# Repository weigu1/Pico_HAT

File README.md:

# Pico-HAT: Connect your Raspi with the Pico through I²C

## All infos on: <http://www.weigu.lu/microcontroller/pico_hat/index.html>

## Some infos

The Pico connects to all the sensors and actuators and can act in `Real Time`. The Raspi can do the rest (Wifi, Webserver, MQTT, Display ...). The Pico is an I²C slave to the Raspi and the Raspi sends commands with a Python script to the Pico. An Arduino program on the Pico answers with sensor data or by switching an actuator.

As the Arduino IDE runs on a Raspi, both device (Raspi and Pico) can be reprogrammed via VNC from any computer, and I find this pretty amazing :).

### Features

+ The Raspi is connected through I²C with the Pico. Serial is prepared if needed (by adding 2 0&#8239;Ω resistors).

+ The Pico can be powered over USB (recommended if you want to reprogram it via Arduino IDE and VNC) or through the Raspi (5&#8239;V).

+ All GPIOs have the possibility to add a voltage divider to reduce the input voltage (e.g. 5&#8239;V to 3.3&#8239;V), or to add an external pull-down resistor.

+ All headers have beneath a ground pin, one or two power pins (3.3&#8239;V or 5&#8239;V; `H2` headers: 3.3&#8239;V and 5&#8239;V).

+ Additionally we get a RESET-button, an `SWD` header, 2 power header (3.3&#8239;V and 5&#8239;V), 2 Ground pins, an an 3V3_EN and ADC\_VREF pins.

### Circuit

The circuit is designed with KiCAD and is open hardware. The following headers are available:

| Name | Pin 1 | Pin 2 | Pin 3 | Pin 5 | Pin 5 | Pin 6 | Pin 7 |
|--|--|--|--|--|--|--|--|
| `5V_Pico` | GND | 5&#8239;V |
| `3V3_Pico` | GND | 3.3&#8239;V |
| `SWD` | SWDIO | GND | SWCLK |
| `H1_ADC0` | GND | ADC0 (GPIO26) | 3.3&#8239;V |
| `H2_ADC1` | GND | ADC1 (GPIO27) | 3.3&#8239;V |
| `H3_ADC2` | GND | ADC2 (GPIO28) | 3.3&#8239;V |
| `H1x1` | GND | GPIO22 | 3.3&#8239;V (or 5&#8239;V) |
| `H3x1` | GND | GPIO13 | 3.3&#8239;V (or 5&#8239;V) |
| `H4x1` | GND | GPIO12 | 3.3&#8239;V (or 5&#8239;V) |
| `H2x1` | GND | GPIO12 | 3.3&#8239;V | 5&#8239;V |
| `H1x2`<br>&#8239; | GND<br>&#8239; | GPIO17<br>(alt. RX0-TX_Raspi) | GPIO16<br>(alt. TX0-RX_Raspi) | 3.3&#8239;V (or 5&#8239;V)<br>&#8239; |
| `H3x2` | GND | GPIO10 | GPIO11 | 3.3&#8239;V (or 5&#8239;V) |
| `H4x2` | GND | GPIO6 | GPIO7 | 3.3&#8239;V (or 5&#8239;V) |
| `H2x2` | GND | GPIO8 | GPIO9 | 3.3&#8239;V | 5&#8239;V |
| `H1x4` | GND | GPIO21 | GPIO20 | GPIO19 | GPIO18 | 3.3&#8239;V (or 5&#8239;V) |
| `H2x4` | GND | GPIO2 | GPIO3 | GPIO4 | GPIO5 | 3.3&#8239;V | 5&#8239;V |

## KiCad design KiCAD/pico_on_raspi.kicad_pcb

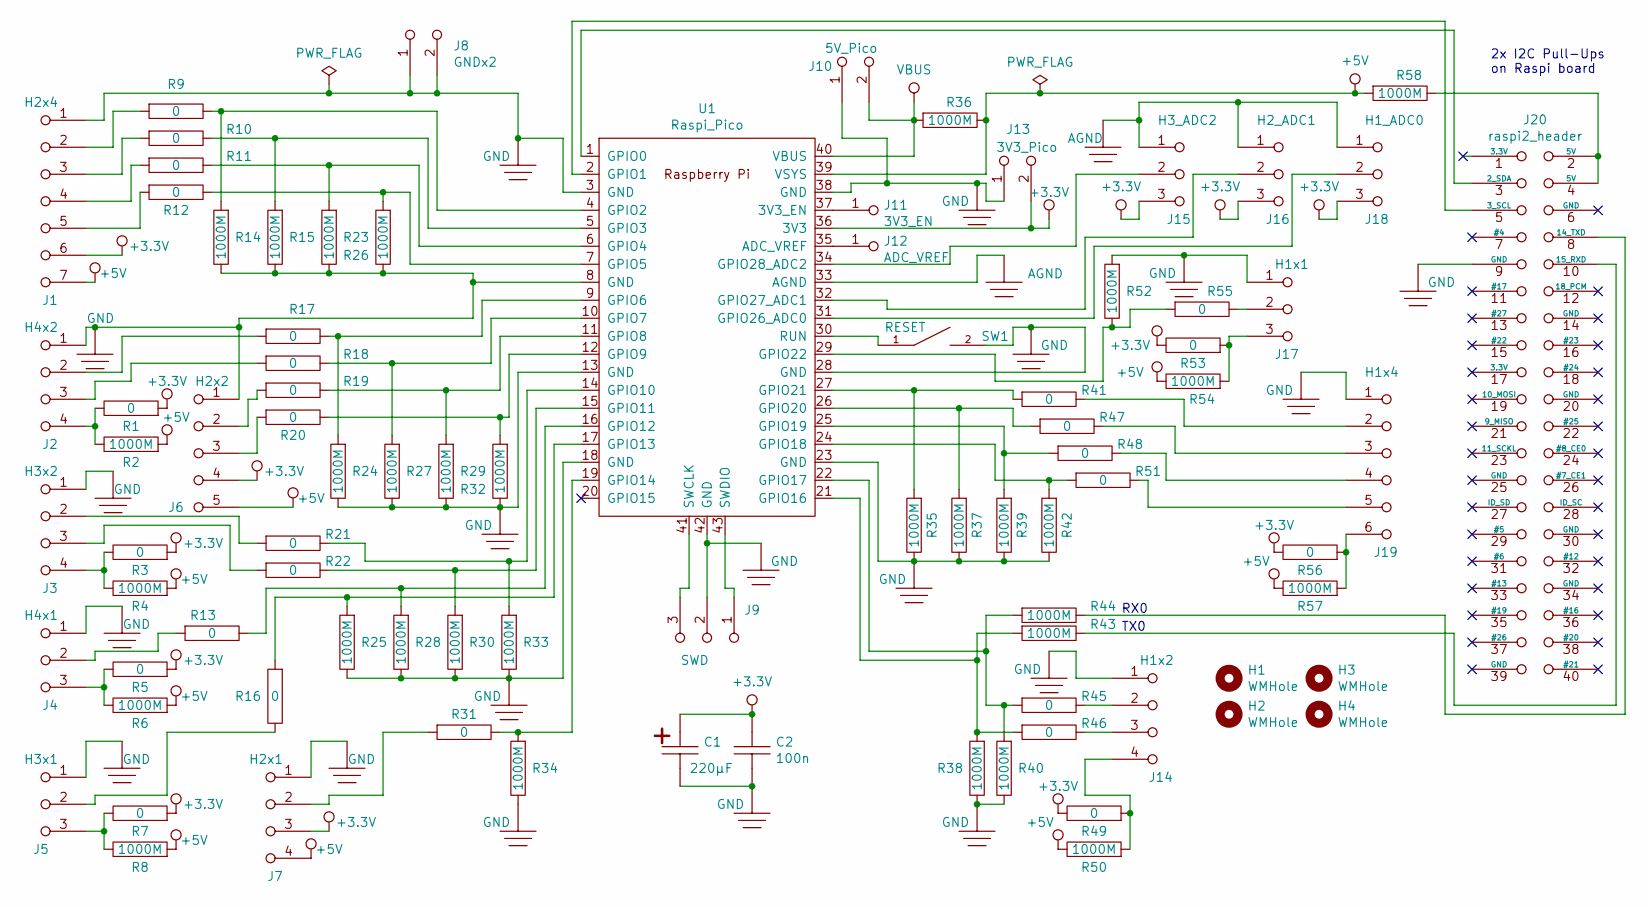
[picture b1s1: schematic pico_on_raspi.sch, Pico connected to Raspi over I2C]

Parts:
C1: 220µF; WC_Elec_SMD_5x5.4
C2: 100n; W0805
H1, H2, H3, H4: WMHole; WHole_2.7mm_M2.5
J1: H2x4; WSIL7_SL
J2: H4x2; WSIL4_SL
J3: H3x2; WSIL4_SL
J4: H4x1; WSIL3_SL
J5: H3x1; WSIL3_SL
J6: H2x2; WSIL5_SL
J7: H2x1; WSIL4_SL
J8: GNDx2; WSIL2_2x1
J9: SWD; WSIL3_SL
J10: 5V_Pico; WSIL2_SL
J11: 3V3_EN; WSIL1
J12: ADC_VREF; WSIL1
J13: 3V3_Pico; WSIL2_SL
J14: H1x2; WSIL4_SL
J15: H3_ADC2; WSIL3_SL
J16: H2_ADC1; WSIL3_SL
J17: H1x1; WSIL3_SL
J18: H1_ADC0; WSIL3_SL
J19: H1x4; WSIL6_SL
J20: raspi2_header; WSIL_2x20_Raspi
R1, R3, R5, R7, R9, R10, R11, R12, R13, R16, R17, R18, R19, R20, R21, R22, R31, R41, R45, R46, R47, R48, R49, R51, R53, R55, R56: 0; W0805_0_Ohm
R2, R4, R6, R8, R14, R15, R23, R24, R25, R26, R27, R28, R29, R30, R32, R33, R34, R35, R36, R37, R38, R39, R40, R42, R43, R44, R50, R52, R54, R57, R58: 1000M; W0805
SW1: RESET; WPB
U1: Raspi_Pico; WPico_RASPI

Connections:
+3.3V: C1.1, C2.1, J1.6 (16), J6.4 (14), J7.3 (13), J13.2 (12), J15.3 (13), J16.3 (13), J18.3 (13), R1.1, R3.1, R5.1, R7.1, R49.2, R53.2, R56.2, U1.36 (3V3)
+5V: J1.7 (17), J6.5 (15), J7.4 (14), R2.1, R4.1, R6.1, R8.1, R36.2, R50.2, R54.2, R57.2, R58.1, U1.39 (VSYS)
unnamed: J1.2 (12), R9.1
unnamed: J1.3 (13), R10.1
unnamed: J1.4 (14), R11.1
unnamed: J1.5 (15), R12.1
unnamed: J2.2 (12), R17.1
unnamed: J2.3 (13), R18.1
unnamed: J2.4 (14), R1.2, R2.2
unnamed: J3.2 (12), R21.1
unnamed: J3.3 (13), R22.1
unnamed: J3.4 (14), R3.2, R4.2
unnamed: J4.2 (12), R13.1
unnamed: J4.3 (13), R5.2, R6.2
unnamed: J5.2 (12), R16.2
unnamed: J5.3 (13), R7.2, R8.2
unnamed: J6.2 (12), R19.1
unnamed: J6.3 (13), R20.1
unnamed: J7.2 (12), R31.1
unnamed: J9.1 (11), U1.43 (SWDIO)
unnamed: J9.3 (13), U1.41 (SWCLK)
unnamed: J10.2 (12), R36.1, U1.40 (VBUS)
unnamed: J11.1, U1.37 (3V3_EN)
unnamed: J12.1, U1.35 (ADC_VREF)
unnamed: J14.2 (12), R45.2
unnamed: J14.3 (13), R46.2
unnamed: J14.4 (14), R49.1, R50.1
unnamed: J15.2 (12), U1.34 (GPIO28_ADC2)
unnamed: J16.2 (12), U1.32 (GPIO27_ADC1)
unnamed: J17.2 (12), R55.2
unnamed: J17.3 (13), R53.1, R54.1
unnamed: J18.2 (12), U1.31 (GPIO26_ADC0)
unnamed: J19.2 (12), R41.2
unnamed: J19.3 (13), R47.2
unnamed: J19.4 (14), R48.2
unnamed: J19.5 (15), R51.2
unnamed: J19.6 (16), R56.1, R57.1
unnamed: J20.2 (5V), J20.4 (5V), R58.2
unnamed: J20.3 (2_SDA), U1.1 (GPIO0)
unnamed: J20.5 (3_SCL), U1.2 (GPIO1)
unnamed: J20.8 (14_TXD), R43.2
unnamed: J20.10 (15_RXD), R44.2
unnamed: R10.2, R15.1, U1.5 (GPIO3)
unnamed: R11.2, R23.1, U1.6 (GPIO4)
unnamed: R12.2, R26.1, U1.7 (GPIO5)
unnamed: R13.2, R28.1, U1.16 (GPIO12)
unnamed: R9.2, R14.1, U1.4 (GPIO2)
unnamed: R16.1, R25.1, U1.17 (GPIO13)
unnamed: R17.2, R24.1, U1.9 (GPIO6)
unnamed: R18.2, R27.1, U1.10 (GPIO7)
unnamed: R19.2, R29.1, U1.11 (GPIO8)
unnamed: R20.2, R32.1, U1.12 (GPIO9)
unnamed: R21.2, R33.1, U1.14 (GPIO10)
unnamed: R22.2, R30.1, U1.15 (GPIO11)
unnamed: R31.2, R34.1, U1.19 (GPIO14)
unnamed: R35.1, R41.1, U1.27 (GPIO21)
unnamed: R37.1, R47.1, U1.26 (GPIO20)
unnamed: R38.1, R44.1, R46.1, U1.21 (GPIO16)
unnamed: R39.1, R48.1, U1.25 (GPIO19)
unnamed: R40.1, R43.1, R45.1, U1.22 (GPIO17)
unnamed: R42.1, R51.1, U1.24 (GPIO18)
unnamed: R52.2, R55.1, U1.29 (GPIO22)
unnamed: SW1.1, U1.30 (RUN)

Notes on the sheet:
RX0
TX0
2x I2C Pull-Ups on Raspi board

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
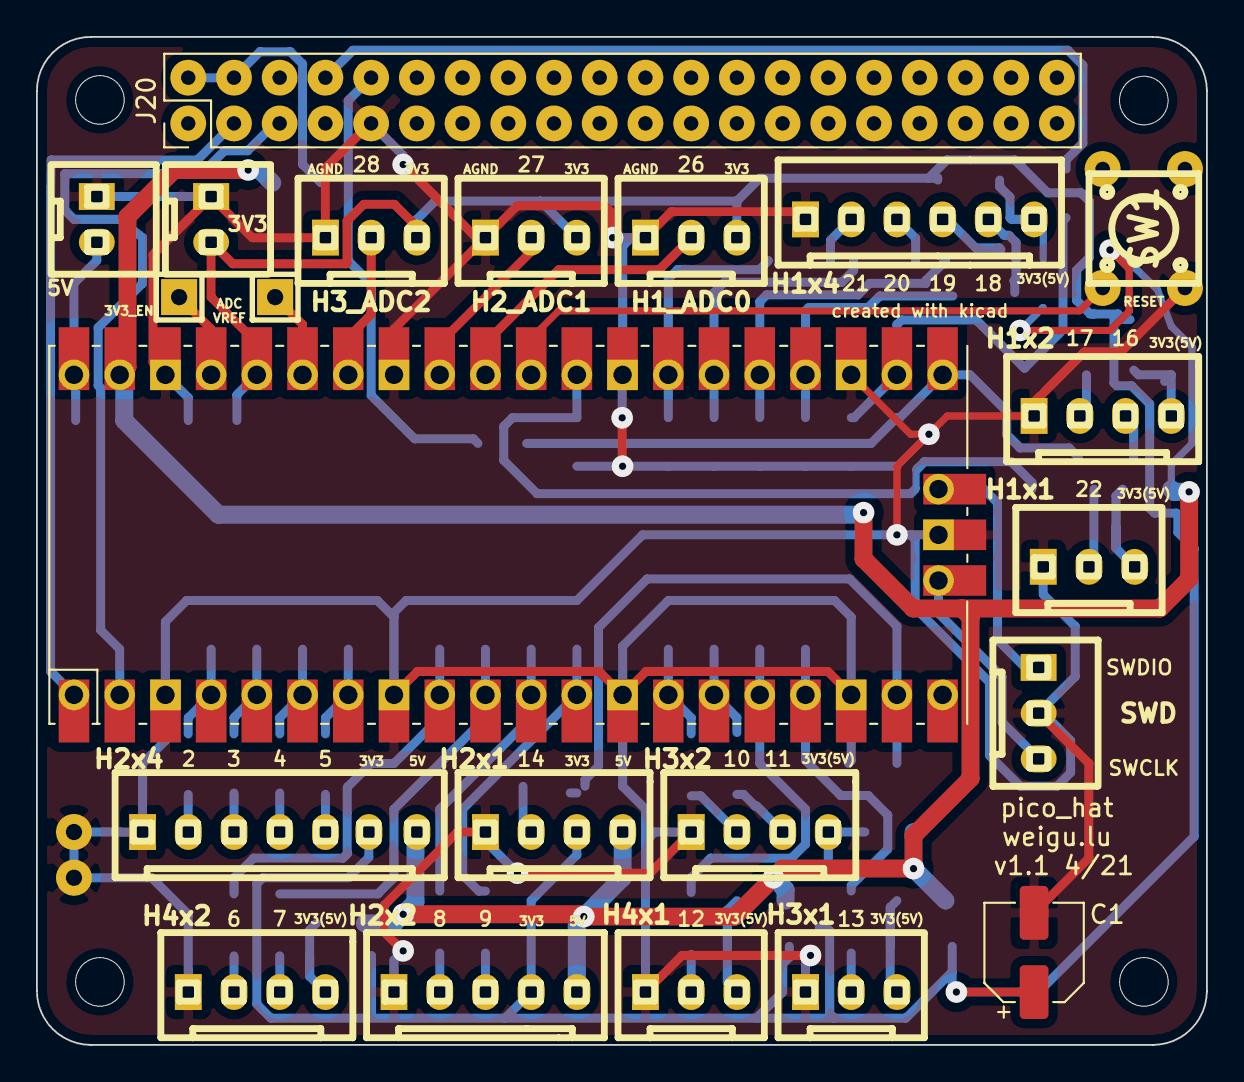
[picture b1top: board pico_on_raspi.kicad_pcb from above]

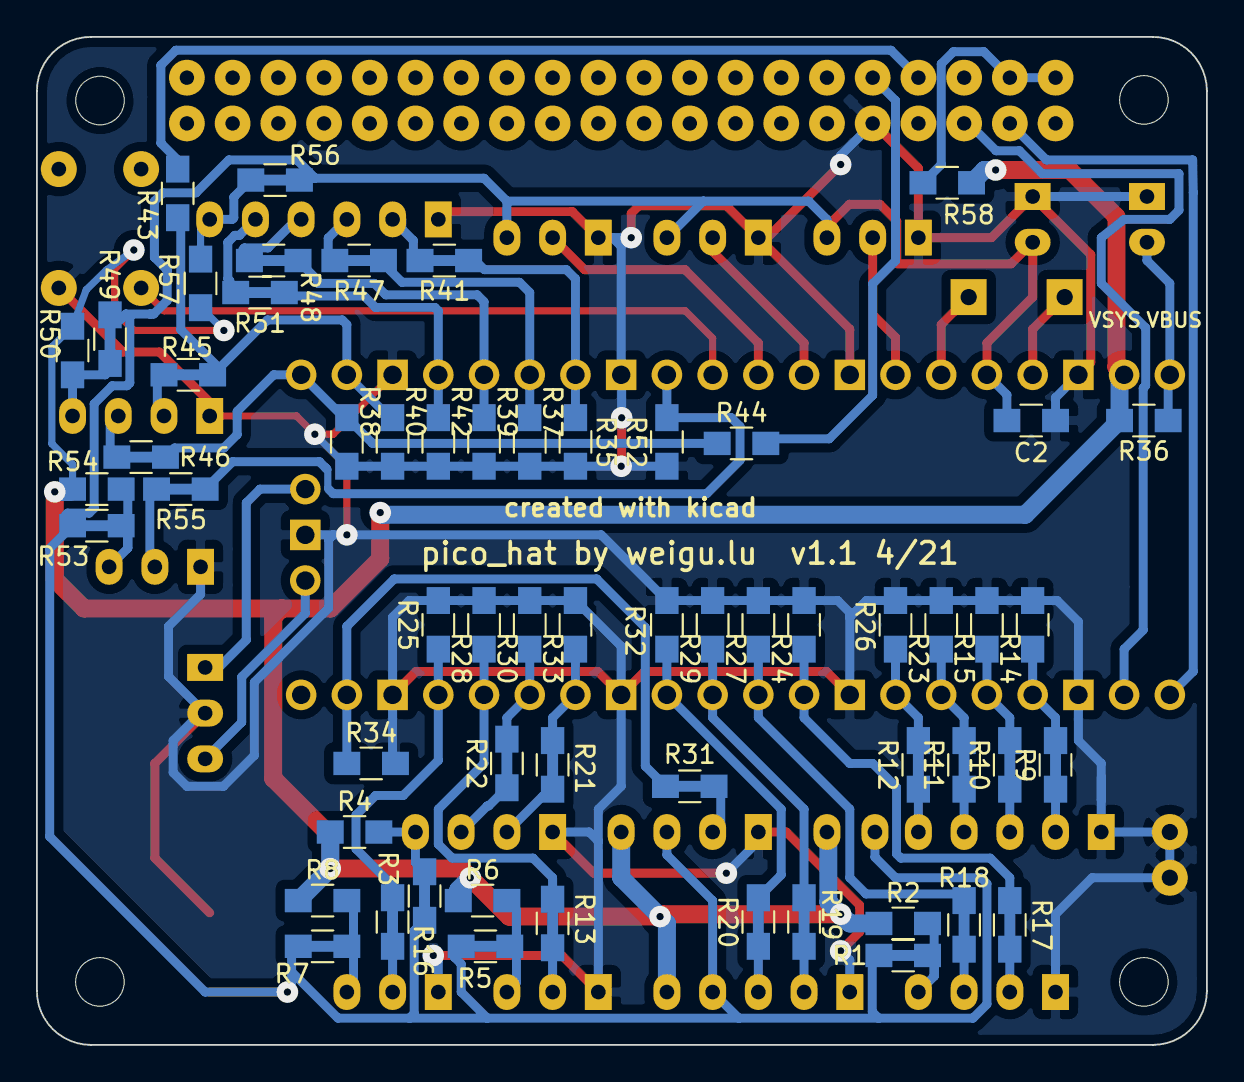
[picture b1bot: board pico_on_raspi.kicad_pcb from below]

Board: 2 copper layers, 65.0 x 56.0 mm, 86 parts (59 on the bottom side), 64 nets.

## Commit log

2021-04-14 changed Readme
2021-04-14 rechanged Readme
